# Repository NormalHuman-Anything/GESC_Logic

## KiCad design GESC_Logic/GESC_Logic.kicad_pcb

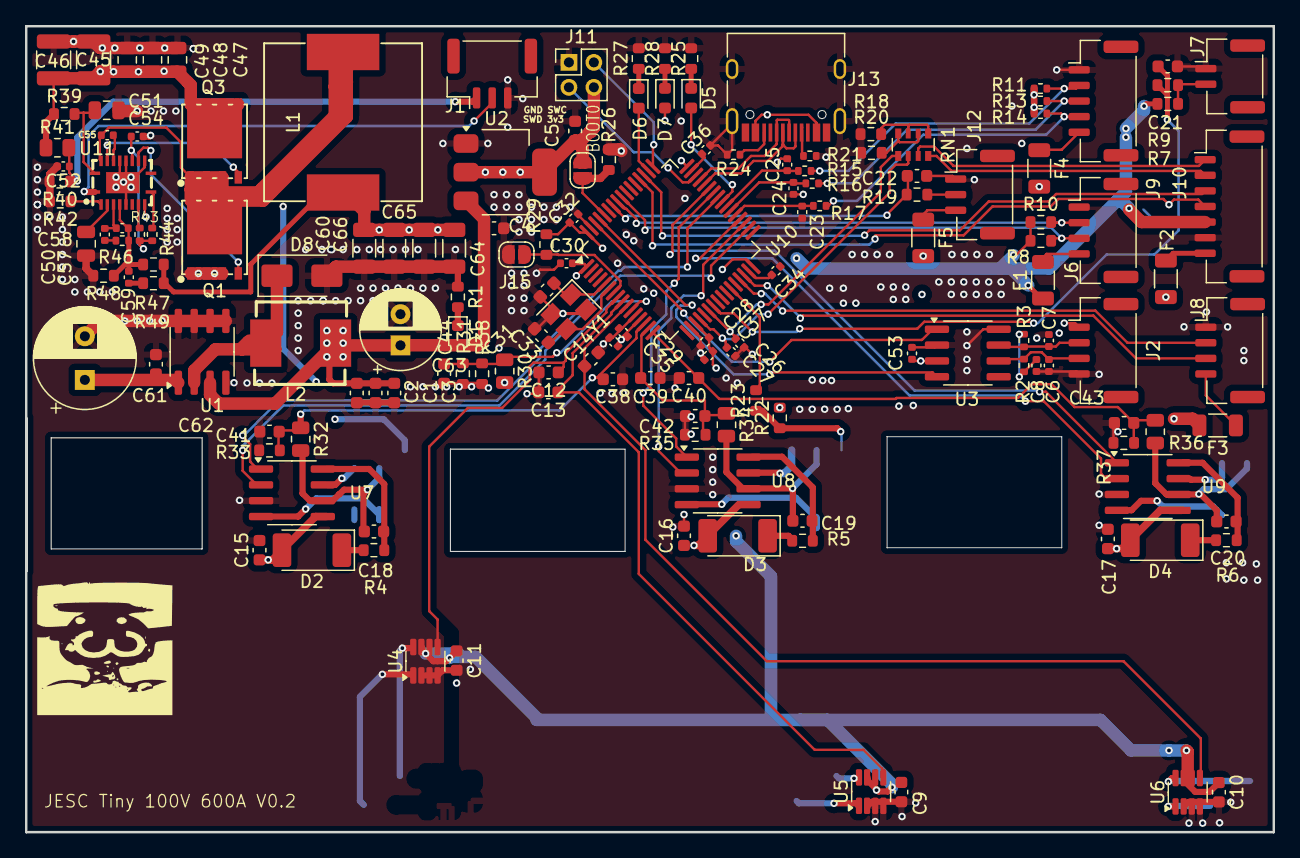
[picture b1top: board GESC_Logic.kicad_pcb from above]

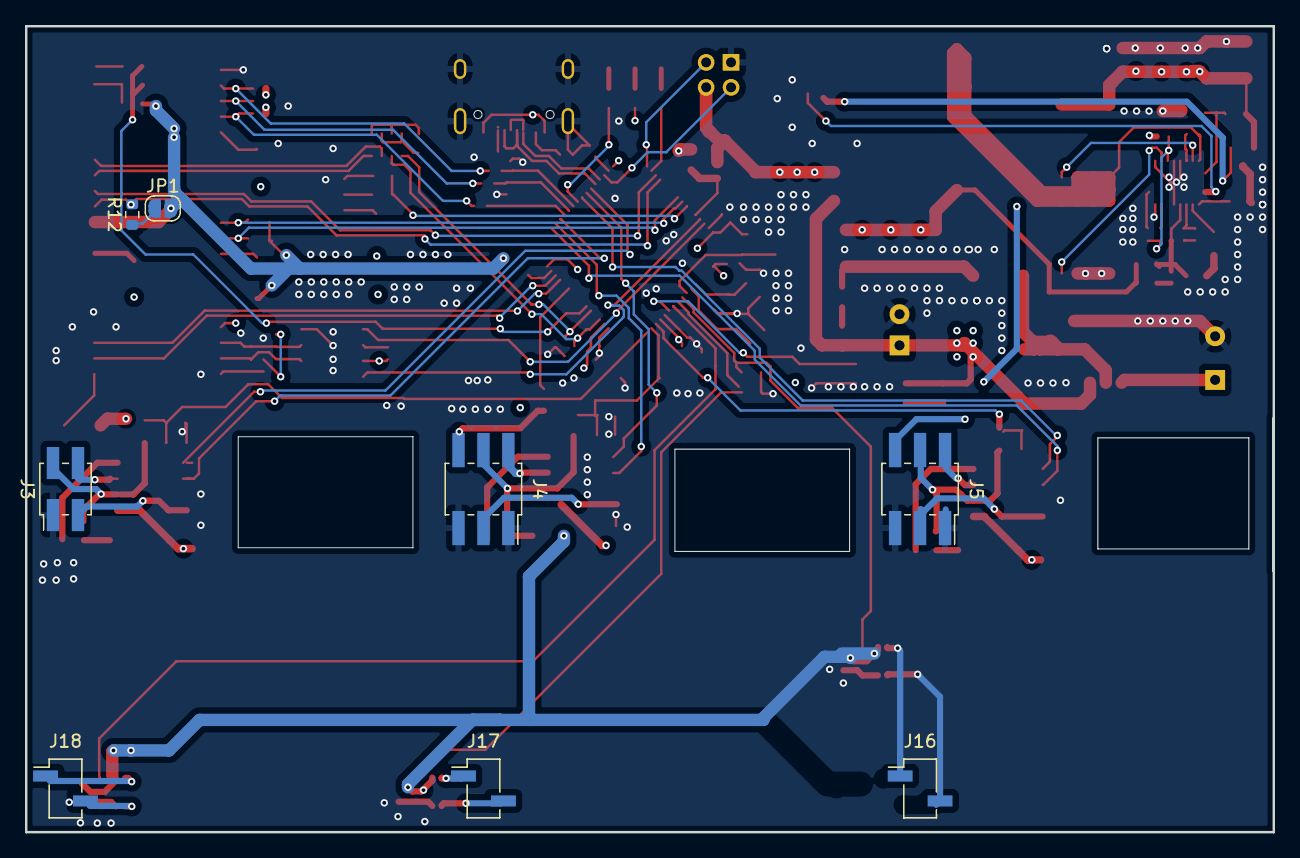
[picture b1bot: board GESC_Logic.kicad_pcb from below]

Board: 4 copper layers, 100.0 x 64.6 mm, 163 parts (8 on the bottom side), 109 nets.

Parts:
BOOT0: BOOT0; SolderJumper-2_P1.3mm_Open_RoundedPad1.0x1.5mm
C1, C2, C3, C18, C19, C20: 10uF; C_0603_1608Metric
C4, C5: 100nf; C_0603_1608Metric
C6, C7: 100p; C_0402_1005Metric
C8: 4.7n; C_0402_1005Metric
C9, C10, C11: 2.2uF; C_0603_1608Metric
C12, C13, C14, C21: 1nF; C_0603_1608Metric
C15, C16, C17, C22, C38, C39, C40: 100nF; C_0603_1608Metric
C23, C24, C25: 1nF; C_0402_1005Metric
C26, C27, C52: 1uF; C_0402_1005Metric
C28, C29, C30, C32, C35, C53, C55, C57: 100nF; C_0402_1005Metric
C31, C33: 12pf; C_0603_1608Metric
C34, C36, C54: 2.2uF; C_0402_1005Metric
C37: 4,7uF; C_0402_1005Metric
C41, C42, C43: 47pF; C_0603_1608Metric
C44: 3.3nF; C_0603_1608Metric
C45, C46: 470nF; C_1210_3225Metric
C47, C48, C49: 1uF; C_0805_2012Metric
C50: 39nF; C_0805_2012Metric
C51: 100nF; C_0805_2012Metric
C58: 68pF; C_0402_1005Metric
C59: 390pF; C_0402_1005Metric
C60, C64, C65, C66: 47uF; C_1206_3216Metric
C61: 470nF; C_0603_1608Metric
C62: 470uF; CP_Radial_D8.0mm_P3.50mm
C63: 180uF; CP_Radial_D6.3mm_P2.50mm
D1: LED; LED_0603_1608Metric
D2, D3, D4: SM4007; D_MELF
D5: R; LED_0603_1608Metric
D6: G; LED_0603_1608Metric
D7: B; LED_0603_1608Metric
D8: 1N5820; D_SMA
F1, F2, F3, F4, F5: 1a; R_1206_3216Metric
Hope it doesn't blow up: LOGO
J1: POWER; JST_GH_BM03B-GHS-TBT_1x03-1MP_P1.25mm_Vertical
J2: CAN; JST_GH_BM04B-GHS-TBT_1x04-1MP_P1.25mm_Vertical
J3: gates_A; PinHeader_2x02_P2.00mm_Vertical_SMD
J4: gates_B; PinSocket_2x03_P2.00mm_Vertical_SMD
J5: gates_C; PinSocket_2x03_P2.00mm_Vertical_SMD
J6: BMI160; JST_GH_BM04B-GHS-TBT_1x04-1MP_P1.25mm_Vertical
J7: TEMP; JST_GH_BM02B-GHS-TBT_1x02-1MP_P1.25mm_Vertical
J8: BMS; JST_GH_BM04B-GHS-TBT_1x04-1MP_P1.25mm_Vertical
J9: HALL; JST_GH_BM05B-GHS-TBT_1x05-1MP_P1.25mm_Vertical
J10: DASH/BLE; JST_GH_BM07B-GHS-TBT_1x07-1MP_P1.25mm_Vertical
J11: STLINK; PinHeader_2x02_P2.00mm_Vertical
J12: PPM; JST_GH_BM03B-GHS-TBT_1x03-1MP_P1.25mm_Vertical
J13: TYPE-C-31-M-12; USB_C_Receptacle_HRO_TYPE-C-31-M-12
J15: NRST; SolderJumper-2_P1.3mm_Open_RoundedPad1.0x1.5mm
J16, J17, J18: SH1; PinSocket_1x02_P2.00mm_Vertical_SMD_Pin1Left
JP1: btn_pullup; SolderJumper-2_P1.3mm_Open_RoundedPad1.0x1.5mm
L1: 4.7uH; IND-SMD_L13.5-W12.8
L2: 68uH; IND-SMD_L7.1-W6.6-1
Q1, Q3: BSC320N20NS3G; DFN-8_L5.9-W5.2-P1.27-LS6.2-BL
R1: 30k; R_0603_1608Metric
R2, R3: 100Ω; R_0402_1005Metric
R4, R5, R6: 2R2; R_0603_1608Metric
R7, R8, R9, R22, R23, R26, R29, R40: 10k; R_0603_1608Metric
R10, R12: 1k; R_0603_1608Metric
R11, R13, R14, R15, R16, R17: 10k; R_0402_1005Metric
R18, R20: 1.8K; R_0603_1608Metric
R19: 100R; R_0603_1608Metric
R21, R24: 5.1k; R_0402_1005Metric
R25, R27, R28: 20k; R_0603_1608Metric
R30, R32, R34, R36: 360k; R_0805_2012Metric
R31: 8k2; R_0603_1608Metric
R33, R35, R37: 8.2k; R_0603_1608Metric
R38: 220k; R_0603_1608Metric
R39: 2.1R; R_0603_1608Metric
R41: 124K; R_0805_2012Metric
R42: 10K; R_0603_1608Metric
R43, R44: 20k; R_0402_1005Metric
R46: 5.23k; R_0402_1005Metric
R47: 18k; R_0603_1608Metric
R48: 1.27K; R_0603_1608Metric
R49: 52.3R; R_0603_1608Metric
RN1: 470R; R_Array_Convex_4x0603
U1: XL1509-5.0; SOIC-8_3.9x4.9mm_P1.27mm
U2: LM1117DT-3.3; SOT-223-3_TabPin2
U3: SN65HVD230DR; SOIC-8_3.9x4.9mm_P1.27mm
U4, U5, U6: INA241; SOT-23-8
U7, U8, U9: L6498DTR; SOIC-8_3.9x4.9mm_P1.27mm
U10: STM32F405RGTx; LQFP-64_10x10mm_P0.5mm
U11: LM5146RGYR; VQFN-20_L4.5-W3.5-P0.50-BL-EP
Y1: 8MHz; Crystal_SMD_3225-4Pin_3.2x2.5mm

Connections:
+3V3: BOOT0.1, C5.1, C9.1, C10.1, C11.1, C28.1, C29.1, C30.1, C32.1, C35.1, C37.1, D7.2 (A), F1.1, J10.5, J11.4, JP1.2 (B), R7.1, R8.1, R10.1, R11.1, R13.1, R14.1, R22.1, R29.1, U2.2 (VO), U4.6 (V+), U4.7 (REF1), U5.6 (V+), U5.7 (REF1), U6.6 (V+), U6.7 (REF1), U10.1 (VBAT), U10.13 (VDDA), U10.19 (VDD), U10.32 (VDD), U10.48 (VDD), U10.64 (VDD)
+5V: C1.1, C2.1, C3.1, C4.1, C53.2, C63.1, D1.2 (A), F2.1, F3.2, F4.2, F5.2, J2.1, L2.2, U1.3 (FB), U2.3 (VI), U3.3 (VCC)
+12V: C15.1, C16.1, C17.1, C60.1, C61.1, C62.1, C64.1, C65.1, C66.1, D2.2 (A), D3.2 (A), D4.2 (A), L1.2, R47.1, R49.1, U1.1 (VIN), U7.5 (VCC), U8.5 (VCC), U9.5 (VCC)
+BATT: C45.1, C46.1, C47.1, C48.1, C49.1, J5.6, Q3.5 (D), Q3.6 (D), Q3.7 (D), Q3.8 (D), R30.2, R39.1, R41.1
/Gate Drivers/AH: U7.1 (HIN), U10.41 (PA8)
/Gate Drivers/AL: U7.2 (LIN), U10.34 (PB13)
/Gate Drivers/BH: U8.1 (HIN), U10.42 (PA9)
/Gate Drivers/BL: U8.2 (LIN), U10.35 (PB14)
/Gate Drivers/CH: U9.1 (HIN), U10.43 (PA10)
/Gate Drivers/CL: U9.2 (LIN), U10.36 (PB15)
ADC1, CS: C27.1, RN1.6 (R3.2), U10.20 (PA4)
ADC2, MISO: C26.1, RN1.5 (R4.2), U10.22 (PA6)
BMI160_SCL: J6.2, R10.2, U10.57 (PB5)
BMI160_SDA: J6.3, R8.2, U10.56 (PB4)
CAN_RXD: U3.4 (RXD), U10.61 (PB8)
CAN_TXD: U3.1 (TXD), U10.62 (PB9)
CURRENT_A: C12.1, U4.5, U10.8 (PC0)
CURRENT_B: C13.1, U5.5, U10.9 (PC1)
CURRENT_C: C14.1, U6.5, U10.10 (PC2)
F_TEMP_: J4.6, R22.2, R23.1
F_Temp: R23.2, U10.27 (PB1)
GND: C1.2, C2.2, C3.2, C4.2, C5.2, C6.2, C7.2, C8.2, C9.2, C10.2, C11.2, C12.2, C13.2, C14.2, C15.2, C16.2, C17.2, C21.2, C22.2, C23.2, C24.2, C25.2, C26.2, C27.2, C28.2, C29.2, C30.2, C31.2, C32.2, C33.2, C34.2, C35.2, C36.2, C37.2, C38.2, C39.2, C40.2, C41.2, C42.2, C43.2, C44.2, C45.2, C46.2, C47.2, C48.2, C49.2, C50.2, C51.2, C52.2, C53.1, C54.2, C60.2, C61.2, C62.2, C63.2, C64.2, C65.2, C66.2, D8.2 (A), J1.3, J2.4, J3.1, J4.1, J4.5, J5.1, J5.5, J6.1, J7.1, J8.1, J9.1, J10.6, J11.1, J12.1, J13.S1 (SHIELD), J15.1, Q1.1 (S), Q1.2 (S), Q1.3 (S), R1.1, R18.1, R20.1, R21.2, R24.2, R25.2, R26.1, R27.2, R28.2, R31.1, R33.1, R35.1, R37.1, R38.1, R40.2, R42.2, R48.2, U1.4 (~EN), U1.5 (GND), U1.6 (GND), U1.7 (GND), U1.8 (GND), U2.1 (GND), U3.2 (GND), U3.8 (S), U4.2 (GND), U4.3 (REF2), U4.4 (GND), U5.2 (GND), U5.3 (REF2), U5.4 (GND), U6.2 (GND), U6.3 (REF2), U6.4 (GND), U7.3 (GND), U8.3 (GND), U9.3 (GND), U10.12 (VSSA), U10.18 (VSS), U10.63 (VSS), U11.6 (AGND), U11.9 (NC), U11.12 (PGND), U11.15 (EP), U11.16 (NC), U11.21 (EP), Y1.2, Y1.4
HALL_A: C23.1, R17.1, U10.37 (PC6)
HALL_B: C24.1, R16.1, U10.38 (PC7)
HALL_C: C25.1, R15.1, U10.39 (PC8)
LED_G: D6.2 (A), U10.50 (PA15)
LED_R: D5.2 (A), U10.40 (PC9)
M_TMP, MOSI: C21.1, R9.1, U10.23 (PA7)
unnamed: C8.1, R2.2, R3.1
unnamed: C57.2, R46.2
unnamed: C59.1, R49.2
unnamed: D1.1 (K), R1.2
unnamed: D2.1 (K), R4.1
unnamed: D3.1 (K), R5.1
unnamed: D4.1 (K), R6.1
unnamed: D5.1 (K), R25.1
unnamed: D6.1 (K), R27.1
unnamed: D7.1 (K), R28.1
unnamed: D8.1 (K), L2.1, U1.2 (OUT)
unnamed: C52.1, J1.1, R40.1, R41.2
unnamed: J1.2, U11.1 (EN/UVLO)
unnamed: C7.1, J2.2, R3.2, U3.7 (CANH)
unnamed: C6.1, J2.3, R2.1, U3.6 (CANL)
unnamed: J3.3, U9.4 (LVG)
unnamed: J3.4, U9.7 (HVG)
unnamed: J4.2, U8.7 (HVG)
unnamed: J4.3, U8.4 (LVG)
unnamed: J5.2, U7.7 (HVG)
unnamed: J5.3, U7.4 (LVG)
unnamed: F1.2, J6.4
unnamed: J7.2, R7.2, R9.2
unnamed: F3.1, J8.4
unnamed: J9.2, R11.2, R15.2
unnamed: J9.3, R13.2, R16.2
unnamed: J9.4, R14.2, R17.2
unnamed: F4.1, J9.5
unnamed: J10.1, RN1.7 (R2.2)
unnamed: J10.2, RN1.8 (R1.2)
unnamed: F2.2, J10.7
unnamed: J12.2, R19.2
unnamed: F5.1, J12.3
unnamed: J13.A5 (CC1), R21.1
unnamed: J13.B5 (CC2), R24.1
unnamed: BOOT0.2, R26.2, U10.60 (BOOT0)
unnamed: J15.2, R29.2, U10.7 (NRST)
unnamed: JP1.1 (A), R12.1
unnamed: Q1.4 (G), U11.13 (LO)
unnamed: Q3.4 (G), U11.18 (HO)
unnamed: R18.2, RN1.1 (R1.1), RN1.3 (R3.1)
unnamed: R20.2, RN1.2 (R2.1), RN1.4 (R4.1)
unnamed: C18.1, R4.2, U7.8 (BOOT)
unnamed: C19.1, R5.2, U8.8 (BOOT)
unnamed: C20.1, R6.2, U9.8 (BOOT)
unnamed: C31.1, U10.5 (PH0), Y1.1
unnamed: C33.1, U10.6 (PH1), Y1.3
unnamed: C34.1, U10.31 (VCAP_1)
unnamed: C36.1, U10.47 (VCAP_2)
unnamed: C55.2, U11.17 (BST)
unnamed: C57.1, C58.1, U11.4 (COMP)
unnamed: C58.2, C59.2, R46.1, R47.2, R48.1, U11.5 (FB)
unnamed: R44.2, U11.10 (PGOOD)
unnamed: R42.1, U11.2 (RT)
unnamed: C50.1, U11.3 (SS/TRK)
unnamed: C55.1, L1.1, Q1.5 (D), Q1.6 (D), Q1.7 (D), Q1.8 (D), Q3.1 (S), Q3.2 (S), Q3.3 (S), U11.19 (SW)
unnamed: R43.2, U11.8 (SYNCIN)
unnamed: C54.1, R43.1, R44.1, U11.14 (VCC)
unnamed: C51.1, R39.2, U11.20 (VIN)
PPM: C22.1, R19.1, U10.58 (PB6)
Phase_A: C18.2, J5.4, R32.2, U7.6 (OUT)
Phase_B: C19.2, J4.4, R34.2, U8.6 (OUT)
Phase_C: C20.2, J3.2, R36.2, U9.6 (OUT)
SHA_+: J16.1, U4.8 (+)
SHA_-: J16.2, U4.1 (-)
SHB_+: J17.1, U5.8 (+)
SHB_-: J17.2, U5.1 (-)
SHC_+: J18.1, U6.8 (+)
SHC_-: J18.2, U6.1 (-)
SWCLK: J11.2, U10.49 (PA14)
SWDIO: J11.3, U10.46 (PA13)
UART_RX: J10.4, R12.2, U10.52 (PC11)
UART_TX: J10.3, U10.51 (PC10)
USART_RX, SDA: J8.3, U10.30 (PB11)
USART_TX, SCL: J8.2, U10.29 (PB10)
USB_D+: J13.A6 (DP1), J13.B6 (DP2), U10.45 (PA12)
USB_D-: J13.A7 (DN1), J13.B7 (DN2), U10.44 (PA11)
VSENSE: C44.1, R30.1, R31.2, R38.2, U10.11 (PC3)
V_A: C38.1, C41.1, R32.1, R33.2, U10.14 (PA0)
V_B: C39.1, C42.1, R34.1, R35.2, U10.15 (PA1)
V_C: C40.1, C43.1, R36.1, R37.2, U10.16 (PA2)

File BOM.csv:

"Reference","Value","Datasheet","Footprint","Qty","DNP","LCSC"
"C1,C2,C3,C18,C19,C20","10uF","~","Capacitor_SMD:C_0603_1608Metric","6","","C96446"
"C4,C5","100nf","~","Capacitor_SMD:C_0603_1608Metric","2","","C14663"
"C6,C7","100p","","Capacitor_SMD:C_0402_1005Metric","2","","C1546"
"C8","4.7n","https://datasheet.lcsc.com/lcsc/1811031110_FH--Guangdong-Fen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","Capacitor_SMD:C_0402_1005Metric","1","","C1538"
"C9,C10,C11","2.2uF","~","Capacitor_SMD:C_0603_1608Metric","3","","C23630"
"C12,C13,C14,C21","1nF","~","Capacitor_SMD:C_0603_1608Metric","4",""," C1588"
"C15,C16,C17,C22,C38,C39,C40","100nF","~","Capacitor_SMD:C_0603_1608Metric","7","","C14663"
"C23,C24,C25","1nF","~","Capacitor_SMD:C_0402_1005Metric","3","","C106205"
"C26,C27,C52","1uF","~","Capacitor_SMD:C_0402_1005Metric","3","","C52923"
"C28,C29,C30,C32,C35,C53,C55,C57","100nF","~","Capacitor_SMD:C_0402_1005Metric","8","","C60474"
"C31,C33","12pf","~","Capacitor_SMD:C_0603_1608Metric","2","","C519482"
"C34,C36,C54","2.2uF","~","Capacitor_SMD:C_0402_1005Metric","3","","C77002"
"C37","4,7uF","~","Capacitor_SMD:C_0402_1005Metric","1","","C368809"
"C41,C42,C43","47pF","~","Capacitor_SMD:C_0603_1608Metric","3","","C1613"
"C44","3.3nF","~","Capacitor_SMD:C_0603_1608Metric","1","","C1613"
"C45,C46","470nF","~","Capacitor_SMD:C_1210_3225Metric","2","","C192761"
"C47,C48,C49","1uF","~","Capacitor_SMD:C_0805_2012Metric","3","","C28323"
"C50","39nF","~","Capacitor_SMD:C_0805_2012Metric","1","","C309493"
"C51","100nF","~","Capacitor_SMD:C_0805_2012Metric","1","","C476766"
"C56","220pF","~","Capacitor_SMD:C_0402_1005Metric","1","","C368809"
"C58","68pF","~","Capacitor_SMD:C_0402_1005Metric","1","","C368809"
"C59","390pF","~","Capacitor_SMD:C_0402_1005Metric","1","","C282239"
"C60,C64,C65,C66","47uF","~","Capacitor_SMD:C_1206_3216Metric","4","","C403725"
"C61","470nF","~","Capacitor_SMD:C_0603_1608Metric","1","","C1623"
"C62","470uF","~","Capacitor_THT:CP_Radial_D8.0mm_P3.50mm","1","DNP","C721169"
"C63","180uF","~","Capacitor_THT:CP_Radial_D6.3mm_P2.50mm","1","DNP"," C2976258"
"D1","LED","~","LED_SMD:LED_0603_1608Metric","1","","C72041"
"D2,D3,D4","SM4007","http://cdn-reichelt.de/documents/datenblatt/A400/SMD1N400%23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","Diode_SMD:D_MELF","3",""," C412437"
"D5","R","~","LED_SMD:LED_0603_1608Metric","1","","C2286"
"D6","G","~","LED_SMD:LED_0603_1608Metric","1","","C87326"
"D7","B","~","LED_SMD:LED_0603_1608Metric","1","","C2689219"
"D8","1N5820","~","Diode_SMD:D_SMA","1",""," C110484"
"F1,F2,F3,F4,F5","1a","~","Resistor_SMD:R_1206_3216Metric","5","","C2982267"
"J1","POWER","~","Connector_JST:JST_GH_BM03B-GHS-TBT_1x03-1MP_P1.25mm_Vertical","1",""," C3029369"
"J2","CAN","~","Connector_JST:JST_GH_BM04B-GHS-TBT_1x04-1MP_P1.25mm_Vertical","1","","C3029370"
"J3","gates_A","~","Connector_PinHeader_2.00mm:PinHeader_2x02_P2.00mm_Vertical_SMD","1","DNP",""
"J4","gates_B","~","Connector_PinSocket_2.00mm:PinSocket_2x03_P2.00mm_Vertical_SMD","1","DNP",""
"J5","gates_C","~","Connector_PinSocket_2.00mm:PinSocket_2x03_P2.00mm_Vertical_SMD","1","DNP",""
"J6","BMI160","~","Connector_JST:JST_GH_BM04B-GHS-TBT_1x04-1MP_P1.25mm_Vertical","1","","C3029370"
"J7","TEMP","~","Connector_JST:JST_GH_BM02B-GHS-TBT_1x02-1MP_P1.25mm_Vertical","1","","C3029368"
"J8","BMS","~","Connector_JST:JST_GH_BM04B-GHS-TBT_1x04-1MP_P1.25mm_Vertical","1","","C3029370"
"J9","HALL","~","Connector_JST:JST_GH_BM05B-GHS-TBT_1x05-1MP_P1.25mm_Vertical","1","","C3029371"
"J10","DASH/BLE","~","Connector_JST:JST_GH_BM07B-GHS-TBT_1x07-1MP_P1.25mm_Vertical","1","","C5340799"
"J12","PPM","~","Connector_JST:JST_GH_BM03B-GHS-TBT_1x03-1MP_P1.25mm_Vertical","1",""," C3029369"
"J13","TYPE-C-31-M-12","https://datasheet.lcsc.com/lcsc/2205251630_Korean-Hroparts-E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","Connector_USB:USB_C_Receptacle_HRO_TYPE-C-31-M-12","1","","C165948"
"J14","BOOT0","~","x`","1","DNP",""
"J15","NRST","~","Jumper:SolderJumper-2_P1.3mm_Open_RoundedPad1.0x1.5mm","1","DNP",""
"JP1","btn_pullup","~","Jumper:SolderJumper-2_P1.3mm_Open_RoundedPad1.0x1.5mm","1","DNP",""
"L1","4.7uH","~","lcsc:IND-SMD_L13.5-W12.8","1","","C5298321"
"L2","68uH","~","lcsc:IND-SMD_L7.1-W6.6-1","1","","C2894721"
"Q1,Q3","BSC320N20NS3G","https://lcsc.com/product-detail/MOSFET_Infineon-Technologies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","lcsc:DFN-8_L5.9-W5.2-P1.27-LS6.2-BL","2","","C501501"
"R1","30k","~","Resistor_SMD:R_0603_1608Metric","1","","C22984"
"R2,R3","100Ω","","Resistor_SMD:R_0402_1005Metric","2","","C25076"
"R4,R5,R6","2R2","~","Resistor_SMD:R_0603_1608Metric","3",""," C22939"
"R7,R8,R9,R22,R23,R26,R29,R40","10k","~","Resistor_SMD:R_0603_1608Metric","8","","C25804"
"R10,R12","1k","~","Resistor_SMD:R_0603_1608Metric","2","","C21190"
"R11,R13,R14,R15,R16,R17","10k","~","Resistor_SMD:R_0402_1005Metric","6","","C25744"
"R18,R20","1.8K","~","Resistor_SMD:R_0603_1608Metric","2","","C4177"
"R19","100R","~","Resistor_SMD:R_0603_1608Metric","1","","C105588"
"R21,R24","5.1k","","Resistor_SMD:R_0402_1005Metric","2","","C105872"
"R25,R27,R28","20k","~","Resistor_SMD:R_0603_1608Metric","3","","C269687"
"R30","360k","~","Resistor_SMD:R_0805_2012Metric","1","","C17645"
"R31","8k2","~","Resistor_SMD:R_0603_1608Metric","1","","C25981"
"R32,R34,R36","150k","~","Resistor_SMD:R_0805_2012Metric","3","","C17645"
"R33,R35,R37","3.3k","~","Resistor_SMD:R_0603_1608Metric","3","","C25981"
"R38","220k","~","Resistor_SMD:R_0603_1608Metric","1","","C22961"
"R39","2.1R","~","Resistor_SMD:R_0603_1608Metric","1","","C482786"
"R41","124K","~","Resistor_SMD:R_0805_2012Metric","1","","C2933298"
"R42","10K","~","Resistor_SMD:R_0603_1608Metric","1","","C25804"
"R43,R44","20k","~","Resistor_SMD:R_0402_1005Metric","2","","C25765"
"R45","59R","~","Resistor_SMD:R_0805_2012Metric","1","","C2999506"
"R46","5.23k","~","Resistor_SMD:R_0402_1005Metric","1","","C25907"
"R47","18k","~","Resistor_SMD:R_0603_1608Metric","1","","C25810"
"R48","1.27K","~","Resistor_SMD:R_0603_1608Metric","1","","C2930048"
"R49","52.3R","~","Resistor_SMD:R_0603_1608Metric","1","","C2998074"
"RN1","470R","~","Resistor_SMD:R_Array_Convex_4x0603","1","","C25510"
"U1","XL1509-5.0","https://datasheet.lcsc.com/lcsc/1809050422_XLSEMI-XL1509-5-0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","Package_SO:SOIC-8_3.9x4.9mm_P1.27mm","1","","C61063"
"U2","LM1117DT-3.3","http://www.ti.com/lit/ds/symlink/lm1117.pdf","Package_TO_SOT_SMD:SOT-223-3_TabPin2","1","","C126027"
"U3","SN65HVD230DR","https://datasheet.lcsc.com/lcsc/1809201810_NXP-Semicon-TJA10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","Package_SO:SOIC-8_3.9x4.9mm_P1.27mm","1","","C12084"
"U4,U5,U6","INA240A1D","http://www.ti.com/lit/ds/symlink/ina240.pdf","Package_SO:SOIC-8_3.9x4.9mm_P1.27mm","3","","C2060769"
"U7,U8,U9","L6498DTR","L6498DTR","lcsc:SOIC-8_L4.9-W3.9-P1.27-LS6.0-BL","3","","C500658"
"U10","STM32F405RGTx","https://www.st.com/resource/en/datasheet/stm32f405rg.pdf","Package_QFP:LQFP-64_10x10mm_P0.5mm","1","","C15742"
"U11","LM5146RGYR","","lcsc:VQFN-20_L4.5-W3.5-P0.50-BL-EP","1","","C3188679"
"Y1","8MHz","~","Crystal:Crystal_SMD_3225-4Pin_3.2x2.5mm","1","","C518154"

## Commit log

2024-12-26 licensechange
2024-12-26 Change LICENSE
2025-01-26 asdf
2025-01-27 Update LICENSE
2025-04-16 adsf
2025-05-05 Final
2025-05-05 fffinal
